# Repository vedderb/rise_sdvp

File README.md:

# VESC Self-Driving Model Vehicle Platform (formerly known as RISE SDVP)

This is the source code and hardware design for a model vehicle platform developed and maintained by the VESC project (formerly at RISE Research Institutes of Sweden). The platform has support for cars with Ackermann steering, robots with differential steering and partial support for quadcopters.

Self-Driving in this context means that the vehicles can follow a pre-programmed path outdoors accurately using RTK-GNSS. The paths can be edited using [RControlStation](Linux/RControlStation) as a set of points with different time stamps or velocities, depending on the mode. It is also possible to send paths to the vehicles with time stamps in real-time from external applications (either using UDP or TCP to RControlStation, or directly over a radio link) for e.g. following other vehicles.

Some details about the position estimation and the autopilot can be found in our [published article](https://www.hindawi.com/journals/jr/2018/4907536/).

Figure 1 shows a screenshot of RControlStation, which is a GUI where model vehicles can be viewed, configured and controlled in real time.

Here is a (quire outdated) video with a test of VESC SDVP on a model car:

## Repository Structure

The repository is organized as follows:

- **Documentation**  
    Contains Markdown files with documentation and tutorials, and the directories:
    - **PDF**  
    Contains generated PDFs from the markdown files. Will be cleared when the documentation is built.
    - **Pictures**  
    Contains photos and drawings, which are referenced in the documentation files.
- **Embedded**  
    Contains embedded software for various PCBs of the platform.
    - **Mote**  
    The software for the mote PCB, which can be used as a USB-to-802.15.4 bridge to communicate with the model cars.
    - **RC_Controller**  
    The software for the control PCB. This is where the sensor fusion, position estimation and autopilot for the car runs.
    - **uwb_board**  
    The software for the Ultra-wideband ranging boards.
- **Hardware**  
    KiCad PCB projects with the PCBs for the platform.
    - **Controller**  
    The PCB that is referred to as the controller in this documentation. The RC_Controller software runs on this one, and this is the main PCB that this platform is built on.
    - **RFMote_PA**  
    The USB-to-802.15.4 bridge mentioned above. Note that if an IP-connection with e.g. a raspberry pi is used, this one is not needed.
    - **uwb_pcb**  
    A PCB with a DWM1000 module, a STM32F4 microcontroller, a MPU9250 IMU, a CAN-transceiver and some DC/DC converters. The uwb_board software mentioned above runs on this one. This PCB is not needed, but it is useful for experimenting with UWB positioning.
- **Linux**  
    Contains Linux software, mostly written using the [Qt framework](https://www.qt.io/), for the platform.
    - **Car_Client**  
    This is a Qt command line program that can run on e.g. a raspberry pi, which is connected to the Controller PCB over USB. Car_Client provides a TCP bridge, which can be used to access the Controller over a network connection instead of a radio. Car_Client also runs the Chronos software (which might be documented later) and can simulate cars for development without having access to a model car. Car_Client can also connect to cameras supported by Video For Linux (V4L) and stream them as JPEG images to RControlStation.
    - **RControlStation**  
    This is a desktop program that can stream realtime data from the cars (including video), and edit trajectories for the model cars on top of OpenStreetMap. It can also act as a RTK base station, or connect to one. There are also many other functions, such as providing a TCP bridge to control cars and even emulating GPS signal using software-defined radio. It is a Qt Creator project, install the following packages under Ubuntu 18.04 or later to build it: `build-essential qtcreator qt5-default qtquickcontrols2-5-dev qtdeclarative5-dev libqt5serialport5-dev`
    - **RControlStationComm**  
    A C library that can be used to interface cars and trajectories from RControlStation, when using the TCP server in RControlStation.
    - **CarNetworkTester**  
    A test program where XML messages that can be decoded by RControlStation can be generated and sent, and the response can be studied. Useful for developing independent programs that interface with RControlStation and the model cars over TCP.
    - **scala_test**  
    Scala and java-based software to perform automatic testing of the model cars in real-time using ScalaCheck. RControlStationComm is used to interface with the cars and RControlStation. An interactive scala shell where the cars can be controlled, including the ability to generate trajectories to arbitrary points and orientations avoiding static obstacles, is also included. A paper where this is presented in detail is currently being written.
    - **Pi**  
    Scripts and UDEV rules for a raspberry pi (or similar) embedded Linux computer that is installed on a model car and runs Car_Client.

## Hardware

Figure 2 shows a hardware diagram of a working configuration of the VESC-SDVP platform. The cyan-colored boxes to the left are the components on a model car, and the green boxes to the right are a laptop computer connected over 4G to the model car. The laptop computer also runs a RTK-GNSS base station, so that the model car can position itself with around 3 cm accuracy relative to the GNSS antenna connected to the receiver on the laptop.

Here is a video that shows how a model car like the one in the block diagram above was built:

There are many different configuration of hardware components that can result in a working VESC SDVP model car. What they need to function in general is:

- The [Controller](Hardware/Controller), which runs the embedded software that controls the motion and estimates the position of the model car.
- A [VESC](https://vesc-project.com) motor controller that controls the motor on the car over CAN-bus, and provides speed and position estimation from the motor that is used in the sensor fusion in the controller.
- A computer that runs the [RControlStation](Linux/RControlStation) software.
- A way to communicate between the [Controller PCB](Hardware/Controller) and [RControlStation](Linux/RControlStation). The options are:
    - Using the embedded radios on the controller, and our [Radio Mote](Hardware/RFMote_PA) plugged in over USB to the computer running RControlStation.
    - Connecting the controller to an embedded Linux computer using USB, such as the [Raspberry PI](https://www.raspberrypi.org/), and running [Car_Client](Linux/Car_Client) on that computer. Then RControlStation can communicate with the controller over TCP using Car_Client. The TCP connection can then run over a network as usual, such as WiFi or 4G cellular. This is the method that we are using on the setup above.
- Correction data from a RTK-SN base station within 10 km from where the car operates. There is support for different sources of correction data, such as:
    - Connecting a supported GNSS receiver, such as the Ublox M8T or Ublox M8P, to the computer running RControlStation, and streaming correction data over that connection. This is what we do in the setup above.
    - Connecting to a NTRIP server. This can be done from RControlStation, or by passing an argument to Car_Client if it is used instead of a radio.
    - Our [Controller](Hardware/Controller) in base station mode, where it will transmit correction data over the 433 MHz radio.
- Other things that are (obviously) needed are motor, steering servo, power supplies and antennas.

## Steering Geometries

There is currently support for two different steering geometries: _Ackermann_ and _Differential_. In Ackermann steering mode there is one main motor driving the car, and a steering servo controlling the direction; whereas in differential mode there is one motor that drives the wheels on each side of the car and there is no steering servo. By default, the controller is configured for Ackermann steering, but that, and many other settings, can be changed in [conf_general.h](Embedded/RC_Controller/conf_general.h):

```
// Set to 1 to enable differential steering
#define HAS_DIFF_STEERING			1
// CAN ID of VESC motor controller for the left motor
#define DIFF_STEERING_VESC_LEFT		0
// CAN ID of VESC motor controller for the right motor
#define DIFF_STEERING_VESC_RIGHT	1
```

In addition to updating _conf_general.h_, geometry parameters for the car also have to be updated in RControlStation, as shown in Figure 3:

The most important parameters for Ackermann steering are listed in the following table. Some of them are not used in differential steering mode.

| Parameter      | Description             |
|--------------  |-----------------------------------------------------------------------------|
| Gear Ratio     | The ratio between one wheel revolution and one motor revolution.            |
| Turn Radius    | The radius of the circle the car follows at maximum steering angle.         |
| Wheel Diameter | Diameter of the model car wheels.                                           |
| Axis Distance  | Distance between front and rear wheel axis.                                 |
| Motor Poles    | Number of motor poles. Usually 2 or 4 for inrunners.                        |
| Servo Center   | PWM signal to output to steering servo when going straight [0 - 1].         |
| Servo Range    | Steering range. Negative numbers invert the servo direction [-1 - 1].       |

It is important to get these parameters correct, as they have a large impact on the position estimation and autopilot.

## Simulation Mode

It is possible to test the platform without having access to any other hardware than a computer. This can be done by running [Car_Client](Linux/Car_Client) with the following flags:

```
./Car_Client --usetcp --simulatecars 1:0
```

This will simulate a model car locally, including the autopilot. Then RControlStation can connecto to localhost over TCP and control the simulated car as if it were an actual model car. Car_Client accepts several different flags that affect the simulation; all flags can be listed using the -h argument:

```
./Car_Client -h
```

## Building and Running Car_Client

Car_Client can be built with

```
cd Linux/Car_Client
qmake -qt=5 DEFINES+=HAS_CAMERA
make clean
make
```
After that Car_Client can be started, and a connection can be made from RControlStation:

```
./Car_Client -p /dev/ttyACM0 --useudp --logusb --usetcp
```

## GPS Emulation using Software-Defined Radio (SDR)

RControlStation also supports generation GPS signals using the [Lime SDR](https://www.crowdsupply.com/lime-micro/limesdr-mini). This is work in progress and planned to be useful for automatic HIL testing in the future, but it might be nice to play around with if you have access to a Lime SDR. In order to use it, the [Lime Suite](https://wiki.myriadrf.org/Lime_Suite) has to be installed on your system. Once that is done, RControlStation can be build with Lime SDR support by uncommenting the following line in RControlStation.pro:

```
# Lime SDR support
#DEFINES += HAS_LIME_SDR
```

Once RControlStation is compiled with Lime SDR support, a real-time GPS simulation can be started from _Tests -> GPS Simulator_, which will show the dialog in Figure 4:

The desired latitude, longitude and height can then simply be set in the dialog. It is also possible to follow a model car and generate its perceived position. The [simulation mode](#SimulationMode) can also be used in combination with the GPS Emulator, making it possible to generate GPS signal for a virtual vehicle in real-time.

## User Guides, Tutorials and other Resources
- A work-in-progress user guide with several details on how to use RControlStation can be found [here](https://github.com/svenssonjoel/rise_sdvp_documentation/raw/master/RControlStationManual/RControlStation_doc_version_0_1.pdf).
- A tutorial on how to implement new functionality both in the embedded control software and in RControlStation can be found [here](https://github.com/svenssonjoel/rise_sdvp_documentation/raw/master/EmbeddedProgrammingExample/main.pdf)
- Our [published article](https://www.hindawi.com/journals/jr/2018/4907536/)

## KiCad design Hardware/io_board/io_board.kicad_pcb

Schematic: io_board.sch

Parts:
C1, C2, C3, C4, C17: 2.2u; C_0603_1608Metric
C9, C14, C15: 100u; CP_Radial_D10.0mm_P5.00mm
D1, D2, D5, D6, D7, D8: D_Schottky; D_SMA
D3: RED; LED_0603_1608Metric
D4: GREEN; LED_0603_1608Metric
H1, H2, H3, H4, H5: MountingHole; MountingHole_3.2mm_M3
J1, J2, J3: Valves; TerminalBlock_Phoenix_PT-1,5-2-5.0-H_1x02_P5.00mm_Horizontal
J4, J5: Steering; TerminalBlock_Phoenix_PT-1,5-2-5.0-H_1x02_P5.00mm_Horizontal
J6, J7: Limit SW; TerminalBlock_Phoenix_PT-1,5-2-5.0-H_1x02_P5.00mm_Horizontal
J8: ADC_IO; TerminalBlock_Phoenix_PT-1,5-2-5.0-H_1x02_P5.00mm_Horizontal
J9, J10: ADC_VDIV; TerminalBlock_Phoenix_PT-1,5-2-5.0-H_1x02_P5.00mm_Horizontal
J11: 12V IN; TerminalBlock_Phoenix_PT-1,5-2-5.0-H_1x02_P5.00mm_Horizontal
J12, J15: CAN; JST_PH_B4B-PH-K_1x04_P2.00mm_Vertical
J13: AS5047; JST_PH_B6B-PH-K_1x06_P2.00mm_Vertical
Q1, Q2, Q3, Q4, Q5, Q6, Q7, Q8, Q9, Q10, Q11, Q12, Q13: Q_NMOS_GSD; SOT-23
R1, R2, R3, R6, R7, R9, R12, R14, R17, R20, R23: 10k; R_0603_1608Metric
R4, R5, R10, R11, R13, R15, R16, R18, R19, R21, R22, R24, R25: 1k; R_0603_1608Metric
R8: 220R; R_0603_1608Metric
U1: AZ1117-3.3; SOT-223
U2: TJA1051TK-3; DFN-8-1EP_3x3mm_P0.65mm_EP1.55x2.4mm

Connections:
+5V: C1.1, C17.1, J12.4, J15.4, U1.3, U2.3 (VCC)
+12V: C9.1, C14.1, D1.1 (K), D2.1 (K), D5.1 (K), D6.1 (K), D7.1 (K), D8.1 (K), J5.1, J11.1, R10.1
/ADC1: J8.1; also elsewhere on the board
/ADC2: J8.2; also elsewhere on the board
/ADC_DIV1: R14.2, R15.1; also elsewhere on the board
/ADC_DIV2: R17.2, R18.1; also elsewhere on the board
/ADC_DIV3: R20.2, R21.1; also elsewhere on the board
/ADC_DIV4: R23.2, R24.1; also elsewhere on the board
/AS_CS: J13.5; also elsewhere on the board
/AS_MISO: J13.4; also elsewhere on the board
/AS_MOSI: J13.2; also elsewhere on the board
/AS_SCK: J13.3; also elsewhere on the board
/CANH: J12.3, J15.3, R8.1, U2.7 (CANH)
/CANL: J12.2, J15.2, R8.2, U2.6 (CANL)
/CAN_RX: U2.4 (RXD); also elsewhere on the board
/CAN_TX: U2.1 (TXD); also elsewhere on the board
/LED_GREEN: D4.2 (A); also elsewhere on the board
/LED_RED: D3.2 (A); also elsewhere on the board
/LIM1: J7.2, R16.2; also elsewhere on the board
/LIM2: J7.1, R19.2; also elsewhere on the board
/LIM3: J6.2, R22.2; also elsewhere on the board
/LIM4: J6.1, R25.2; also elsewhere on the board
/SP: R12.2, R13.1; also elsewhere on the board
/VALVE1: Q1.1 (G), Q2.1 (G), R1.1; also elsewhere on the board
/VALVE2: Q3.1 (G), Q4.1 (G), R2.1; also elsewhere on the board
/VALVE3: Q5.1 (G), Q6.1 (G), R3.1; also elsewhere on the board
/VALVE4: Q7.1 (G), Q8.1 (G), R6.1; also elsewhere on the board
/VALVE5: Q9.1 (G), Q10.1 (G), R7.1; also elsewhere on the board
/VALVE6: Q11.1 (G), Q13.1 (G), R9.1; also elsewhere on the board
/VALVE_STEERING: Q12.1 (G); also elsewhere on the board
GND: C1.2, C2.2, C3.2, C4.2, C9.2, C14.2, C15.2, C17.2, J5.2, J11.2, J12.1, J13.6, J15.1, Q1.2 (S), Q2.2 (S), Q3.2 (S), Q4.2 (S), Q5.2 (S), Q6.2 (S), Q7.2 (S), Q8.2 (S), Q9.2 (S), Q10.2 (S), Q11.2 (S), Q12.2 (S), Q13.2 (S), R1.2, R2.2, R3.2, R4.1, R5.1, R6.2, R7.2, R9.2, R13.2, R15.2, R18.2, R21.2, R24.2, U1.1, U2.2 (GND), U2.8 (S), U2.9 (GND); also elsewhere on the board
unnamed: C4.1, J4.1, R11.1
unnamed: D1.2 (A), J1.1, Q1.3 (D), Q2.3 (D)
unnamed: D2.2 (A), J1.2, Q3.3 (D), Q4.3 (D)
unnamed: D3.1 (K), R4.2
unnamed: D4.1 (K), R5.2
unnamed: D5.2 (A), J2.1, Q5.3 (D), Q6.3 (D)
unnamed: D6.2 (A), J2.2, Q7.3 (D), Q8.3 (D)
unnamed: D7.2 (A), J3.1, Q9.3 (D), Q10.3 (D)
unnamed: D8.2 (A), J3.2, Q11.3 (D), Q13.3 (D)
unnamed: J4.2, R12.1
unnamed: J9.1, R14.1
unnamed: J9.2, R17.1
unnamed: J10.1, R20.1
unnamed: J10.2, R23.1
unnamed: Q12.3 (D), R10.2, R11.2
VCC: C2.1, C3.1, C15.1, J13.1, R16.1, R19.1, R22.1, R25.1, U1.2, U2.5 (VIO); also elsewhere on the board

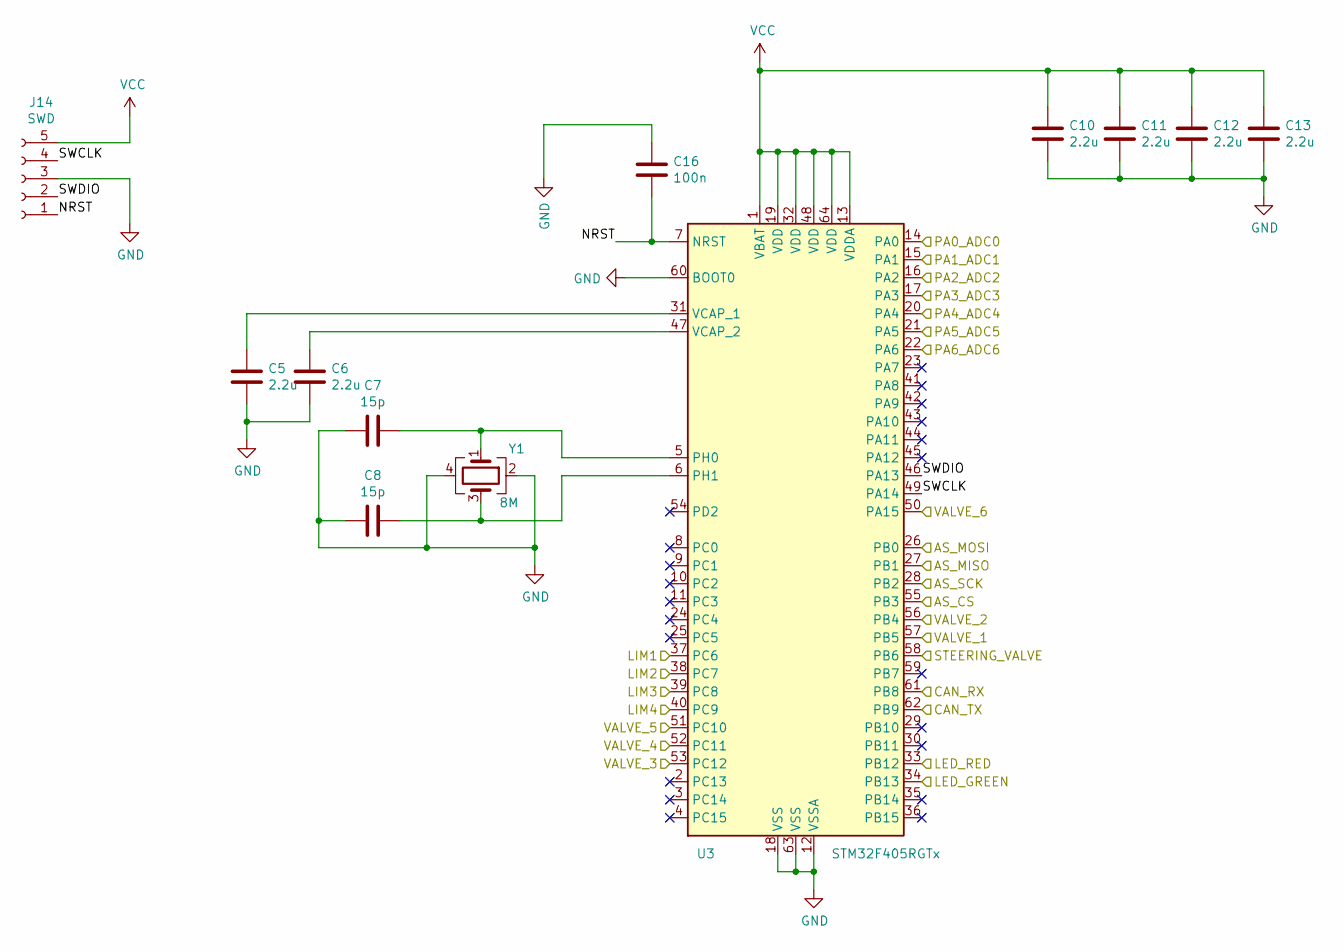
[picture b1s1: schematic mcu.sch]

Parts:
C5, C6, C10, C11, C12, C13: 2.2u; C_0603_1608Metric
C7, C8: 15p; C_0603_1608Metric
C16: 100n; C_0603_1608Metric
J14: SWD; JST_PH_B5B-PH-K_1x05_P2.00mm_Vertical
U3: STM32F405RGTx; LQFP-64_10x10mm_P0.5mm
Y1: 8M; Crystal_SMD_Abracon_ABM3C-4Pin_5.0x3.2mm

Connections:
/ADC1: U3.20 (PA4); also elsewhere on the board
/ADC2: U3.21 (PA5); also elsewhere on the board
/ADC_DIV1: U3.14 (PA0); also elsewhere on the board
/ADC_DIV2: U3.15 (PA1); also elsewhere on the board
/ADC_DIV3: U3.16 (PA2); also elsewhere on the board
/ADC_DIV4: U3.17 (PA3); also elsewhere on the board
/AS_CS: U3.55 (PB3); also elsewhere on the board
/AS_MISO: U3.27 (PB1); also elsewhere on the board
/AS_MOSI: U3.26 (PB0); also elsewhere on the board
/AS_SCK: U3.28 (PB2); also elsewhere on the board
/CAN_RX: U3.61 (PB8); also elsewhere on the board
/CAN_TX: U3.62 (PB9); also elsewhere on the board
/LED_GREEN: U3.34 (PB13); also elsewhere on the board
/LED_RED: U3.33 (PB12); also elsewhere on the board
/LIM1: U3.37 (PC6); also elsewhere on the board
/LIM2: U3.38 (PC7); also elsewhere on the board
/LIM3: U3.39 (PC8); also elsewhere on the board
/LIM4: U3.40 (PC9); also elsewhere on the board
/SP: U3.22 (PA6); also elsewhere on the board
/VALVE1: U3.57 (PB5); also elsewhere on the board
/VALVE2: U3.56 (PB4); also elsewhere on the board
/VALVE3: U3.53 (PC12); also elsewhere on the board
/VALVE4: U3.52 (PC11); also elsewhere on the board
/VALVE5: U3.51 (PC10); also elsewhere on the board
/VALVE6: U3.50 (PA15); also elsewhere on the board
/VALVE_STEERING: U3.58 (PB6); also elsewhere on the board
/mcu/NRST: C16.2, J14.1, U3.7 (NRST)
/mcu/SWCLK: J14.4, U3.49 (PA14)
/mcu/SWDIO: J14.2, U3.46 (PA13)
GND: C5.2, C6.2, C7.2, C8.2, C10.2, C11.2, C12.2, C13.2, C16.1, J14.3, U3.12 (VSSA), U3.18 (VSS), U3.60 (BOOT0), U3.63 (VSS), Y1.2, Y1.4; also elsewhere on the board
unnamed: C5.1, U3.31 (VCAP_1)
unnamed: C6.1, U3.47 (VCAP_2)
unnamed: C7.1, U3.5 (PH0), Y1.1
unnamed: C8.1, U3.6 (PH1), Y1.3
VCC: C10.1, C11.1, C12.1, C13.1, J14.5, U3.1 (VBAT), U3.13 (VDDA), U3.19 (VDD), U3.32 (VDD), U3.48 (VDD), U3.64 (VDD); also elsewhere on the board

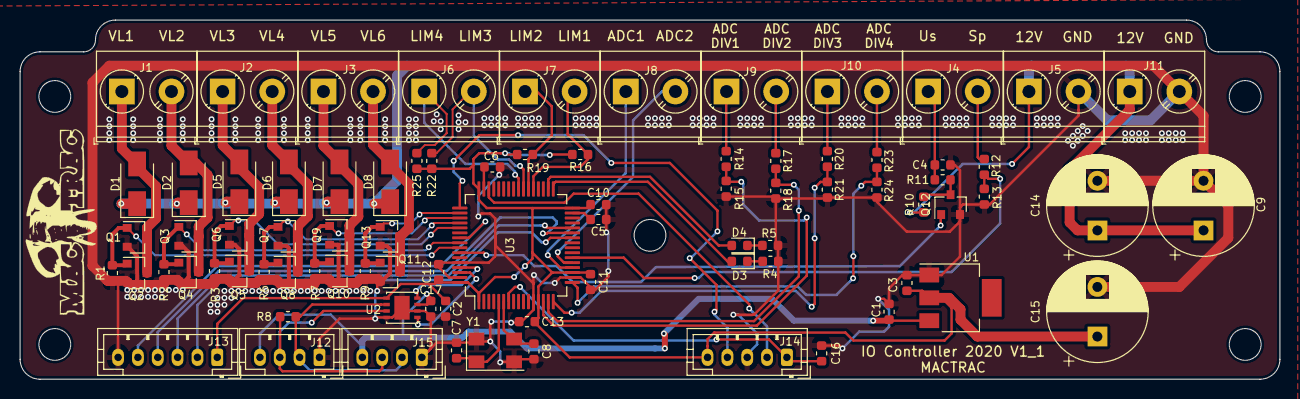
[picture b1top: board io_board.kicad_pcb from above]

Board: 2 copper layers, 127.0 x 36.2 mm, 87 parts (0 on the bottom side), 54 nets.

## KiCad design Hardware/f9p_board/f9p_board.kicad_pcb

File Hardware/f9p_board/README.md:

## UBLOX ZED F9P based positioning controller (Work in progress!).

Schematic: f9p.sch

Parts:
C22: 100n; C_0603_1608Metric
C23, C24, C25: 2.2u; C_0603_1608Metric
D1: RED; LED_0603_1608Metric
L2: 56n; L_0603_1608Metric
R3: 100K; R_0603_1608Metric
R4, R5: 22R; R_0603_1608Metric
R11: 1k; R_0603_1608Metric
R12: 4.7R; R_0603_1608Metric
U1: Ublox_ZED_F9P; UBLOX_ZED_F9P
U7: uFL_conn; U.FL_Molex_MCRF_73412-0110_Vertical

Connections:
F9P_3v3: R3.1, U1.38 (V_USB); also elsewhere on the board
F9P_RESET_N: U1.49 (RESET_N); also elsewhere on the board
F9P_USB_DM: R4.1; also elsewhere on the board
F9P_USB_DP: R5.1; also elsewhere on the board
GND: C22.2, C23.1, C24.1, C25.1, R3.2, R11.2, U1.0, U1.1 (GND), U1.3 (GND), U1.12 (GND), U1.14 (GND), U1.32 (GND), U1.37 (GND), U1.41 (GND), U1.48 (GND), U7.2; also elsewhere on the board
MCU_RX_F9P_TX: U1.42 (TXD_SPI_MISO); also elsewhere on the board
MCU_TX_F9P_RX: U1.43 (RXD_SPI_MOSI); also elsewhere on the board
unnamed: C22.1, L2.2, R12.2
unnamed: D1.1, R11.1
unnamed: D1.2, U1.20 (RTK_STAT)
unnamed: L2.1, U1.2 (RF_IN_1), U7.1
unnamed: R4.2, U1.39 (USB_DM)
unnamed: R5.2, U1.40 (USB_DP)
unnamed: R12.1, U1.7 (VCC_RF)
TIMEPULSE: U1.53 (TIMEPULSE); also elsewhere on the board
VCC: C23.2, C24.2, C25.2, U1.33 (VCC), U1.34 (VCC), U1.36 (V_BCKP); also elsewhere on the board

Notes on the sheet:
DSEL 1 (or open) | 0 42 UART TX | SPI_MISO 43 UART RX | SPI_MOSI 44 I2C Data | SPI CS 45 I2C_CLOCK | SPI_CLK
Host-interface UART
Correction UART RX/TX
Output
Input (Active low)
Input (Active high)

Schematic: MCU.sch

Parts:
C8, C9: 15p; C_0603_1608Metric
C10, C11, C12, C13, C14, C15, C16, C17, C18, C19, C20, C26: 2.2u; C_0603_1608Metric
C21: 100n; C_0603_1608Metric
D2: RED; LED_0603_1608Metric
D3: GREEN; LED_0603_1608Metric
H1, H2, H3, H4: MountingHole; MountingHole_3.2mm_M3
J1, J2: USB_B_Mini; USB_Mini-B_Lumberg_2486_01_Horizontal
J4: CAN; JST_PH_B4B-PH-K_1x04_P2.00mm_Vertical
J7: SERV_0; PinHeader_1x03_P2.54mm_Vertical
J8: SERV_1; PinHeader_1x03_P2.54mm_Vertical
J9: SERV_2; PinHeader_1x03_P2.54mm_Vertical
J10: SERV_3; PinHeader_1x03_P2.54mm_Vertical
P1: SWD; JST_PH_B6B-PH-K_1x06_P2.00mm_Vertical
R6, R7, R9, R10: 1k; R_0603_1608Metric
R8, R21, R22, R23, R24: 220R; R_0603_1608Metric
R13, R14: 22R; R_0603_1608Metric
SW3: BOOT0; SW_SPDT_PCM12
U2: STM32F405RGTx; LQFP-64_10x10mm_P0.5mm
U5: BMI160; Bosch_LGA-14_3x2.5mm_P0.5mm; digikey 828-1057-1-ND
U6: TJA1051TK-3; DFN-8-1EP_3x3mm_P0.65mm_EP1.55x2.4mm
Y1: 8Mhz; Crystal_SMD_5032-4Pin_5.0x3.2mm

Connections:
CANH: J4.3, R8.1, U6.7
CANL: J4.2, R8.2, U6.6
CAN_RX: U2.61, U6.4
CAN_TX: U2.62, U6.1
F9P_RESET_N: U2.40; also elsewhere on the board
F9P_USB_DM: J1.2; also elsewhere on the board
F9P_USB_DP: J1.3; also elsewhere on the board
F9P_USB_VBUS: J1.1; also elsewhere on the board
GND: C8.1, C9.1, C10.2, C11.2, C12.2, C13.2, C14.2, C15.2, C16.2, C17.2, C18.2, C19.2, C20.2, C21.1, C26.1, D2.1, D3.1, J1.5, J1.6, J2.5, J2.6, J4.1, J7.3, J8.3, J9.3, J10.3, P1.4, SW3.1, U2.12, U2.18, U2.28, U2.63, U5.1, U5.6, U5.7, U6.2, U6.8, U6.9, Y1.2, Y1.4; also elsewhere on the board
IMU_INT2: U2.57, U5.9
LED0: R6.2, U2.51
LED1: R7.2, U2.52
MCU_RX_F9P_TX: U2.38; also elsewhere on the board
MCU_TX_F9P_RX: U2.37; also elsewhere on the board
MCU_USB_DM: J2.2, R13.1
MCU_USB_DP: J2.3, R14.1
MCU_USB_VBUS: J2.1; also elsewhere on the board
NRST: C21.2, P1.2, U2.7
unnamed: C8.2, U2.6, Y1.3
unnamed: C9.2, U2.5, Y1.1
unnamed: C10.1, U2.31
unnamed: C11.1, U2.47
unnamed: D2.2, R6.1
unnamed: D3.2, R7.1
unnamed: J7.1, R21.1
unnamed: J8.1, R22.1
unnamed: J9.1, R23.1
unnamed: J10.1, R24.1
unnamed: R13.2, U2.44
unnamed: R14.2, U2.45
unnamed: R21.2, U2.26
unnamed: R22.2, U2.27
unnamed: SW3.2, U2.60
PWR_5V: C26.2, J4.4, J7.2, J8.2, J9.2, J10.2, U2.42, U6.3; also elsewhere on the board
SCL: R10.2, U2.29, U5.13
SDA: R9.2, U2.30, U5.14
SERV_2: R23.2, U2.16
SERV_3: R24.2, U2.17
SWCLK: P1.5, U2.49
SWDIO: P1.3, U2.46
TIMEPULSE: U2.39; also elsewhere on the board
VCC: C12.1, C13.1, C14.1, C15.1, C16.1, C17.1, C18.1, C19.1, C20.1, P1.6, R9.1, R10.1, SW3.3, U2.1, U2.13, U2.19, U2.32, U2.48, U2.64, U5.5, U5.8, U5.12, U6.5; also elsewhere on the board
VOLT_METER: U2.8; also elsewhere on the board

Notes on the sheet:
place close to pin 1, 19, 32, 48, 64, 13
Dubbelkoll CSB - VCC. vi ska ha I2c
Place near VDD/GND BMI160
PC0 - PC5 has ADC
Servo connectors

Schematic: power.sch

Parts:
C1, C2, C5, C6, C7, C35, C36, C37: 2.2u; C_0603_1608Metric
C3: 100n; C_0603_1608Metric
C4: 100u; CP_EIA-3528-12_Kemet-T
C27: 0.01u; C_0603_1608Metric
C28, C29, C30, C31: 2.2u; C_1206_3216Metric
C32: 4700p; C_0603_1608Metric
C33, C40: 0.1u; C_0603_1608Metric
C34: 47p; C_0603_1608Metric
C38: 100u; CP_Radial_D10.0mm_P5.00mm
C39: 470u; CP_Radial_D10.0mm_P5.00mm
J3: BAT_CONN; TerminalBlock_Phoenix_PT-1,5-2-5.0-H_1x02_P5.00mm_Horizontal
J5: USB_A_PWR_OUTPUT; USB_A_Stewart_SS-52100-001_Horizontal
J6: EN_BAT_VIN; JST_PH_B2B-PH-K_1x02_P2.00mm_Vertical
L1: 22u; L_Taiyo-Yuden_MD-5050
L3: 7.2u; L_12x12mm_H8mm
Q1: DMN62D0UW-7; SOT-323_SC-70
R1: 33k; R_0603_1608Metric
R2: 10k; R_0603_1608Metric
R15: 243k; R_0603_1608Metric
R16: 16.9k; R_0603_1608Metric
R17: 39k; R_0603_1608Metric
R18: 2.2k; R_0603_1608Metric
R19: 53.6k; R_0603_1608Metric
R20: 10.2k; R_0603_1608Metric
SW1: F9P_USB_POWER; SW_SPDT_PCM12
SW2: MCU_USB_POWER; SW_SPDT_PCM12
U3: MCP16311MS; MSOP-8_3x3mm_P0.65mm
U4: ncv8705; WDFN6
U8: TPS54561DPRR; TI-DPR; digikey 296-40803-1-ND
U9: PDS760-13; POWERDI5

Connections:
BAT_VIN: C28.1, C29.1, C30.1, C31.1, C38.1, J3.2, R17.1, U8.2
F9P_3v3: C6.1, U4.1; also elsewhere on the board
F9P_USB_VBUS: C7.1, SW1.1, U4.4, U4.6; also elsewhere on the board
FB: R19.1, R20.2, U8.6
GND: C1.2, C2.2, C4.2, C5.2, C6.2, C7.2, C27.2, C28.2, C29.2, C30.2, C31.2, C32.2, C34.2, C35.2, C36.2, C37.2, C38.2, C39.2, C40.2, J3.1, J5.4, J5.5, J6.1, R2.1, R15.2, R18.2, R20.1, U3.5, U3.8, U4.3, U4.GND, U8.8, U8.11, U9.1, U9.2; also elsewhere on the board
MCU_USB_VBUS: SW2.1; also elsewhere on the board
unnamed: C2.1, U3.2
unnamed: C3.1, U3.7
unnamed: C3.2, L1.2, U3.6
unnamed: C27.1, U8.4
unnamed: C32.1, R16.2
unnamed: C33.1, U8.1
unnamed: C34.1, R16.1, U8.7
unnamed: J6.2, U8.3
unnamed: Q1.3, R17.2
unnamed: R1.1, R2.2, U3.1
unnamed: R15.1, U8.5
PWR_5V: C1.1, C35.1, C36.1, C37.1, C39.1, J5.1, L3.2, Q1.1, R19.2, SW1.2, SW2.2, U3.3, U3.4; also elsewhere on the board
SW: C33.2, L3.1, U8.9, U9.3
VCC: C4.1, C5.1, L1.1, R1.2; also elsewhere on the board
VOLT_METER: C40.1, Q1.2, R18.1; also elsewhere on the board

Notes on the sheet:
5v USB Power
3.3V and max 0.5A
3.3V and 1A
The EN pin has an internal pull-up that enables the TPS54561 if the pin is left flaoting.
Kanske behövs sådär 1206 capar
https://katalog.we-online.de/pbs/datasheet/7447709100.pdf
3.2V at 60V BAT_VIN
12061C225KAT2A CAP CER 2.2UF 100V X7R 1206 C3216X7S2A225K160AB CAP CER 2.2UF 100V X7S 1206
RHS = RLS * ((VOUT - 0.8) / 0.8) RHS = RLS * ((5 - 0.8) / 0.8) RHS = RLS * (4.2 / 0.8) RHS = RLS * 5.25 53.55 = 10.2 * 5.25
RHS
RLS
Compensating for the smaller caps with a larger electrolyte

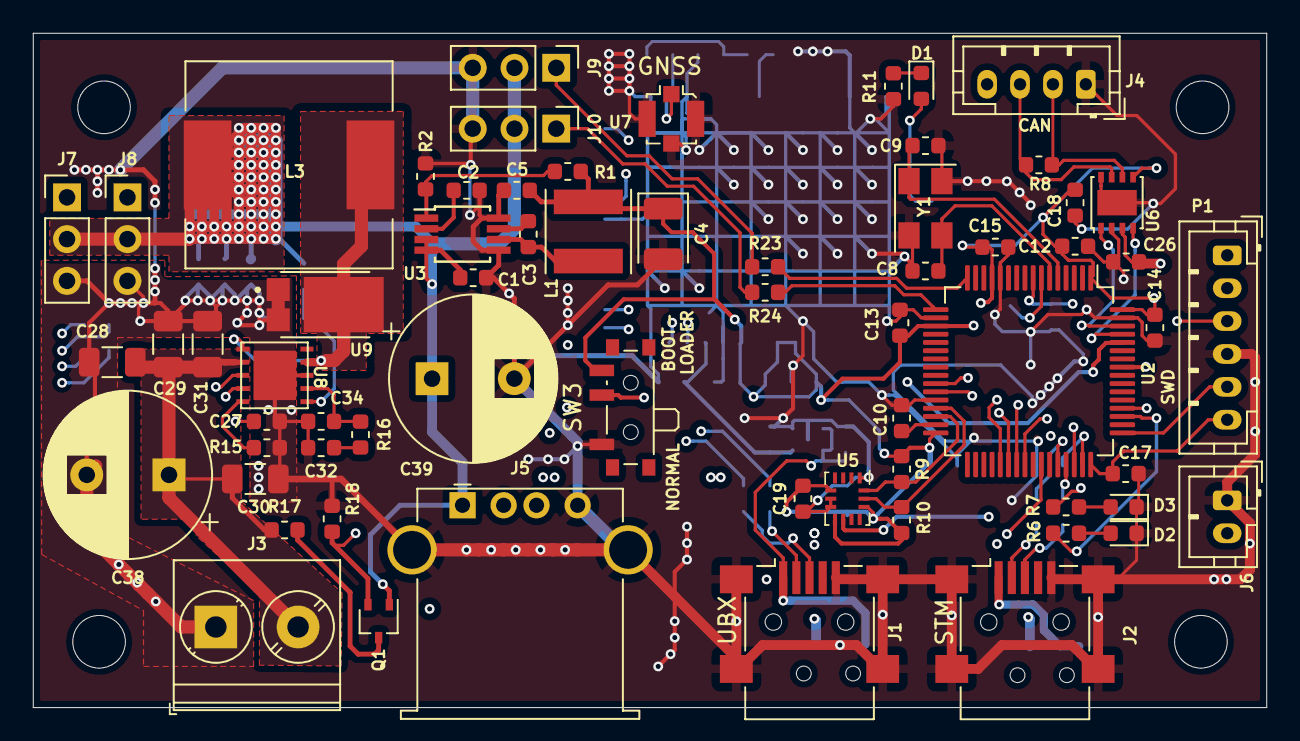
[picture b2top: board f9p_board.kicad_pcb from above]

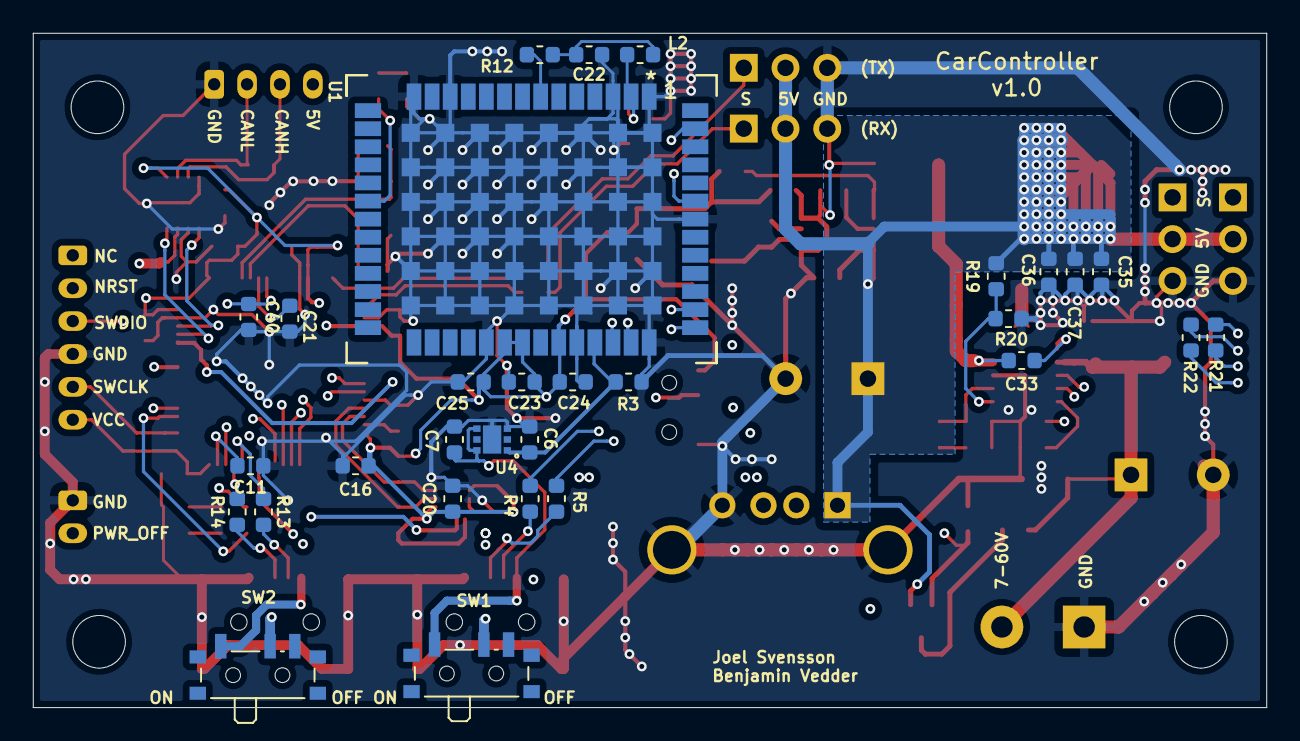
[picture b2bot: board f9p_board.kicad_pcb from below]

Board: 4 copper layers, 75.0 x 41.0 mm, 99 parts (30 on the bottom side), 65 nets.

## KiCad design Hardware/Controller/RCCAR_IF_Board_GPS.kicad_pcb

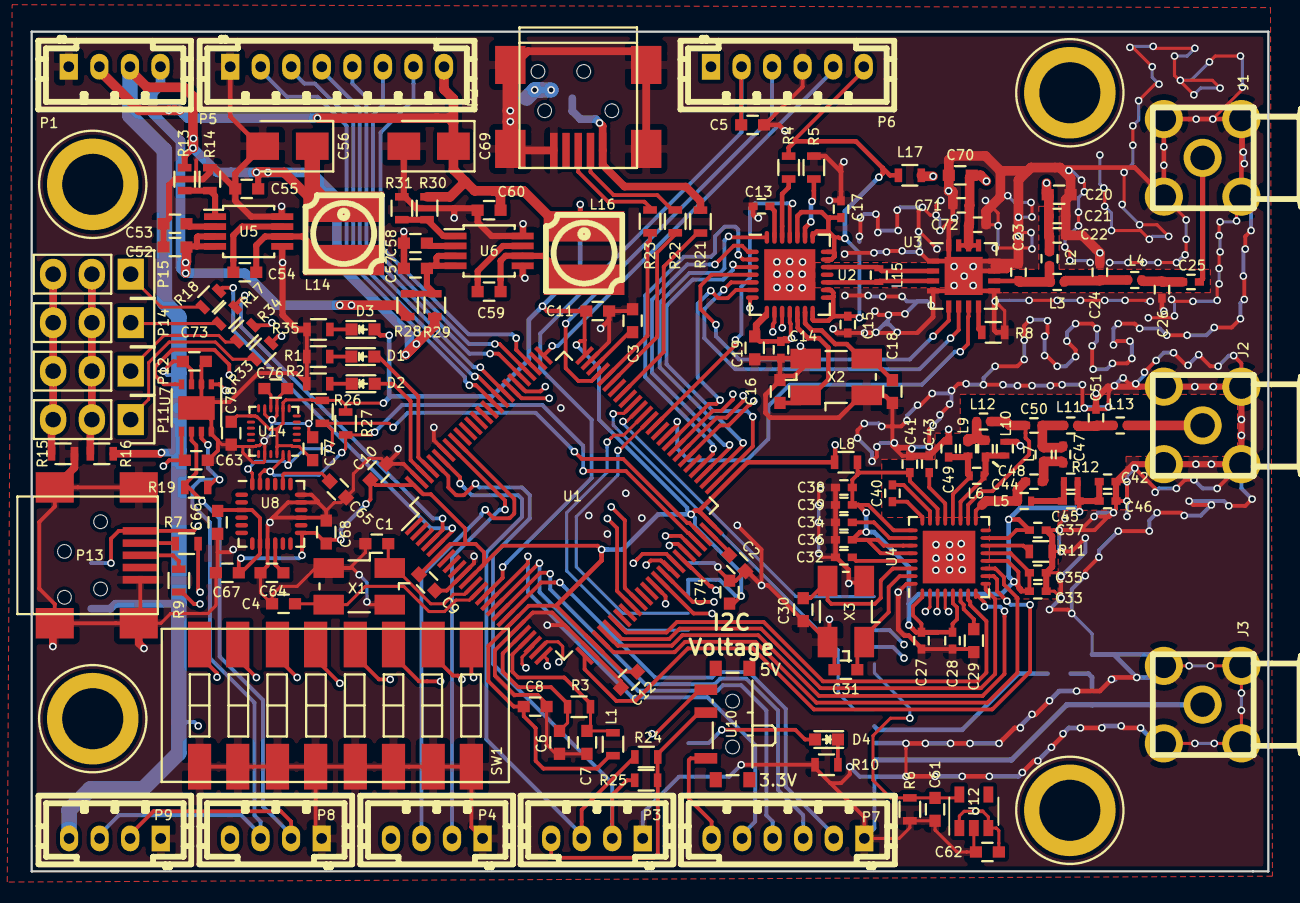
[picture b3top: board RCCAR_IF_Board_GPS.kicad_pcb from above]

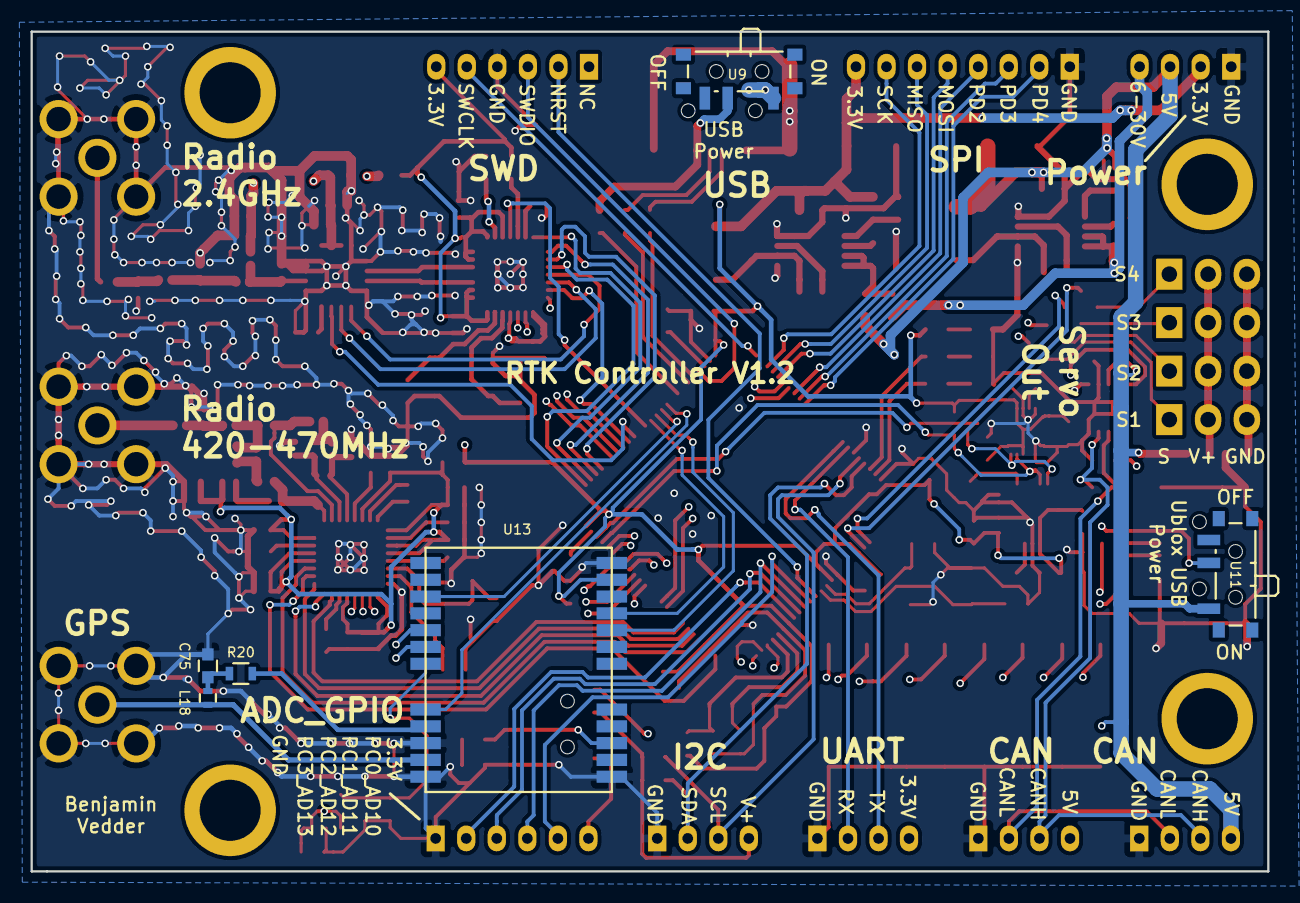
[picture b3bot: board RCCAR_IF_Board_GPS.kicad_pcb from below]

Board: 4 copper layers, 81.0 x 55.0 mm, 173 parts (6 on the bottom side), 143 nets.

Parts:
1PIN, 1PIN#2, 1PIN#3, 1PIN#4: P***; 1pin_4mm
C1, C4, C16, C18, C30, C31: 15p; C_0603
C2, C3, C6, C7, C8, C9, C10, C11, C12, C19, C20, C29, C52, C53, C55, C57, C58, C60, C61, C62, C63, C64, C66, C67, C68, C70, C73, C74, C77, C78: 2.2u; C_0603
C5, C54, C59, C65, C75, C76: 100n; C_0603
C13, C14, C15, C17, C27, C28, C32, C33, C34, C35, C36, C37, C38, C39, C41, C42, C43: 100n; C_0402
C21, C71: 1n; C_0402
C22, C72: 12p; C_0402
C23, C24, C47: 2.2p; C_0402
C25: 18p; C_0402
C26: 0.2p; C_0402
C40: 1.8n; C_0402
C44: 39p; C_0402
C45: 56p; C_0402
C46: 100p; C_0402
C48, C49, C50: 5.1p; C_0402
C51: 6.2p; C_0402
C56, C69: 100u; Tantalum_Case-B_EIA-3528-21_Wave
D1, D4: RED; LED_0603
D2: GREEN; LED_0603
D3: BLUE; LED_0603
J1, J2, J3: SMA; sma_90_crf
L1, L8, L17: BEAD; R_0603
L2: 4.7n; R_0402
L3: 1n; R_0402
L4: 2n; R_0402
L5, L6, L18: 56n; R_0402
L7, L12: 15n; R_0402
L9, L10: 27n; R_0402
L11: 43n; R_0402
L13: 22n; R_0402
L14, L16: 22U; inductor_smd_4.8x2.8mm
L15: DNM; R_0402
P1: POWER; b4b-ph-kl
P2: USB_STM; USB_Mini-B
P3: I2C; b4b-ph-kl
P4: UART; b4b-ph-kl
P5: NRF_SPI; b8b-ph-kl
P6: SWD; b6b-ph-kl
P7: ADC_GPIO; b6b-ph-kl
P8, P9: CAN; b4b-ph-kl
P11: OUT_1; Pin_Header_Straight_1x03
P12: OUT_2; Pin_Header_Straight_1x03
P13: USB_UBLOX; USB_Mini-B
P14: OUT_3; Pin_Header_Straight_1x03
P15: OUT_4; Pin_Header_Straight_1x03
R1, R2, R6, R10, R24, R25, R26, R27, R35: 1k; R_0603
R3: 4R7; R_0603
R4, R14, R31: 10k; R_0603
R5, R11: 56k; R_0603
R7, R9, R21, R22, R23: 22R; R_0603
R8: 3.9k; R_0603
R12: 18R; R_0402
R13: 52.3k; R_0603
R15, R16, R28, R29: 0R; R_0603
R17, R18, R19, R33, R34: 220R; R_0603
R20: 4.7R; R_0603
R30: 33k; R_0603
SW1: Address; SW_DIP_SMD_x8_Slide
U1: STM32F40X_LQFP100; LQFP-100_14x14mm_Pitch0.5mm
U2: CC2520; QFN-28-1EP_5x5mm_Pitch0.5mm
U3: CC2592; QFN-16-1EP_4x4mm_Pitch0.65mm
U4: CC1120; QFN-32-1EP_5x5mm_Pitch0.5mm
U5, U6: MCP16311/2; MSOP-8_3x3mm_Pitch0.65mm
U7: TJA1051TK3; DFN-8-1EP_3x3mm_Pitch0.65mm
U8: MPU9150; QFN-24-1EP_4x4mm_Pitch0.5mm
U9, U11: USB_SUPPLY; SW_SPDT_PCM12
U10: I2C_VOLTAGE; SW_SPDT_PCM12
U12: AP131-33; SOT-23-5
U13: ublox_neo_m8p; ublox_neo
U14: MPU9250; QFN-24_3x3mm_Pitch0.4mm
X1: 8M; Crystal_SMD_5032_4Pads
X2, X3: 32M; Crystal_SMD_5032_4Pads

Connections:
+5V: C55.1, C56.1, C73.1, L14.1, P1.3, P8.4, P9.4, R13.2, R16.1, R29.2, U7.3, U9.1, U10.3, U11.1
+BATT: C52.1, P1.4, R28.2, U5.3, U5.4
/CAN/CANH: P8.3, P9.3, R19.1, U7.7
/CAN/CANL: P8.2, P9.2, R19.2, U7.6
/CAN/CAN_RX: U1.81, U7.4
/CAN/CAN_TX: U1.82, U7.1
/CC1120/CS_N: U1.29, U4.11
/CC1120/GPIO0: U1.26, U4.10
/CC1120/GPIO2: U1.25, U4.4
/CC1120/GPIO3: U1.24, U4.3
/CC1120/V_REG: C27.1, C28.1, C33.1, C35.1, C36.1, C37.1, C38.1, C39.1, C41.1, C42.1, C45.2, C46.1, L8.1, R12.2, U4.1, U4.5, U4.12, U4.13, U4.15, U4.22, U4.25, U4.27, U4.28
/CC2520/CC_CS_N: U1.51, U2.3
/CC2520/CC_GPIO0: U1.56, U2.10
/CC2520/CC_GPIO1: U1.57, U2.9
/CC2520/CC_GPIO2: U1.58, U2.7
/CC2520/CC_GPIO3: U1.59, U2.6
/CC2520/CC_RESET: U1.62, U2.25
/CC2520/CC_SCLK: U1.52, U2.28
/CC2520/CC_SI: U1.54, U2.2
/CC2520/CC_SO: U1.53, U2.1
/CC2520/HGM: U1.60, U3.7
/CC2520/LNA_EN: U2.5, U3.6
/CC2520/PA_EN: U2.4, U3.5
/CC2520/VDD_CC2592: C20.2, C21.2, C22.2, C70.2, C71.2, C72.2, L2.2, L17.2, U3.13, U3.14, U3.15
/MCU/NRST: C5.2, P6.2, U1.14
/MCU/PA0: U1.23, U4.2
/MCU/PA5_SCK1: U1.30, U4.8
/MCU/PA6_MISO1: U1.31, U4.9
/MCU/PA7_MOSI1: U1.32, U4.7
/MCU/PB6_TX1: P4.3, U1.92
/MCU/PB7_RX1: P4.2, U1.93
/MCU/PB8_SCL1: P3.3, R24.2, U1.95
/MCU/PB9_SDA1: P3.2, R25.2, U1.96
/MCU/PB10_SCL2: R27.1, U1.47, U8.23, U14.23
/MCU/PB11_SDA2: R26.1, U1.48, U8.24, U14.24
/MCU/PC0_ADC123_IN10: P7.5, U1.15
/MCU/PC1_ADC123_IN11: P7.4, U1.16
/MCU/PC2_ADC123_IN12: P7.3, U1.17
/MCU/PC3_ADC123_IN13: P7.2, U1.18
/MCU/PC6_TX6: U1.63, U13.21
/MCU/PC7_RX6: U1.64, U13.20
/MCU/PC8: U1.65, U13.3
/MCU/PC9: U1.66, U13.8
/MCU/PC10_SCK3: P5.7, U1.78
/MCU/PC11_MISO3: P5.6, U1.79
/MCU/PC12_MOSI3: P5.5, U1.80
/MCU/PD2: P5.4, U1.83
/MCU/PD3: P5.3, U1.84
/MCU/PD4: P5.2, U1.85
/MCU/PE0: D1.2, U1.97
/MCU/PE1: D2.2, U1.98
/MCU/PE8: SW1.16, U1.39
/MCU/PE9: SW1.15, U1.40
/MCU/PE10: SW1.14, U1.41
/MCU/PE11: SW1.13, U1.42
/MCU/PE12: SW1.12, U1.43
/MCU/PE13: SW1.11, U1.44
/MCU/PE14: SW1.10, U1.45
/MCU/PE15: SW1.9, U1.46
/MCU/SWCLK: P6.5, U1.76
/MCU/SWDIO: P6.3, U1.72
/MCU/USB_DM: R22.1, U1.70
/MCU/USB_DP: R23.1, U1.71
/MCU/USB_VP: R21.1, U1.68
/SERVO_IO/OUT_1: R33.2, U1.35
/SERVO_IO/OUT_2: R34.2, U1.36
/SERVO_IO/OUT_3: R17.2, U1.4
/SERVO_IO/OUT_4: R18.2, U1.5
/ublox/RTK_STAT: D4.2, U13.15
/ublox/USB_DM: R7.2, U13.5
/ublox/USB_DP: R9.2, U13.6
/ublox/VDD_USB: C61.1, R6.1, U12.5, U13.7
GND: C1.2, C2.1, C3.1, C4.2, C5.1, C6.2, C7.1, C8.1, C9.1, C10.1, C11.1, C12.1, C13.1, C14.1, C15.1, C16.2, C17.1, C18.2, C19.1, C20.1, C21.1, C22.1, C23.1, C24.1, C26.1, C27.2, C28.2, C29.1, C30.1, C31.1, C32.1, C33.2, C34.1, C35.2, C36.2, C37.2, C38.2, C39.2, C41.2, C42.2, C43.2, C46.2, C49.1, C51.2, C52.2, C53.2, C55.2, C56.2, C57.2, C58.2, C60.2, C61.2, C62.2, C63.2, C64.2, C65.2, C66.1, C67.1, C68.1, C69.2, C70.1, C71.1, C72.1, C73.2, C74.2, C75.2, C76.2, C77.2, C78.2, J1.2, J2.2, J3.2, L10.1, P1.1, P2.5, P2.6, P3.1, P4.1, P5.1, P6.4, P7.1, P8.1, P9.1, P13.5, P13.6, R1.2, R2.2, R5.2, R6.2, R8.2, R10.2, R11.2, R14.1, R15.1, R31.1, R35.2, SW1.1, SW1.2, SW1.3, SW1.4, SW1.5, SW1.6, SW1.7, SW1.8, U1.10, U1.20, U1.27, U1.74, U1.94, U1.99, U2.29, U3.1, U3.4, U3.9, U3.11, U3.12, U3.16, U3.17, U4.32, U4.33, U5.5, U5.8, U6.5, U6.8, U7.2, U7.8, U7.9, U8.9, U8.15, U8.17, U8.18, U12.2, U13.10, U13.12, U13.13, U13.24, U14.9, U14.11, U14.18, U14.20, X1.3, X2.3, X3.3
unnamed: C1.1, U1.12, X1.1
unnamed: C2.2, U1.49
unnamed: C3.2, U1.73
unnamed: C4.1, U1.13, X1.2
unnamed: C6.1, R3.2, U1.21
unnamed: C7.2, L1.2, R3.1, U1.22
unnamed: C13.2, U2.27
unnamed: C16.1, U2.12, X2.1
unnamed: C18.1, U2.13, X2.2
unnamed: C23.2, L2.1, L3.1, U3.10
unnamed: C24.2, L3.2, L4.1
unnamed: C25.1, C26.2, L4.2
unnamed: C25.2, J1.1
unnamed: C29.2, U4.6
unnamed: C30.2, U4.30, X3.2
unnamed: C31.2, U4.31, X3.1
unnamed: C32.2, U4.29
unnamed: C34.2, U4.26
unnamed: C40.1, U4.24
unnamed: C40.2, U4.23
unnamed: C43.1, U4.21
unnamed: C44.1, C47.2, L7.2
unnamed: C44.2, L5.1, U4.17
unnamed: C45.1, L5.2, R12.1
unnamed: C47.1, C50.2, L7.1, L11.2
unnamed: C48.1, L9.1, L12.1
unnamed: C48.2, L6.2, L10.2, U4.19
unnamed: C49.2, L6.1, L9.2, U4.20
unnamed: C50.1, L12.2, U4.18
unnamed: C51.1, L11.1, L13.2
unnamed: C53.1, U5.2
unnamed: C54.1, U5.7
unnamed: C54.2, L14.2, U5.6
unnamed: C57.1, R28.1, R29.1, U6.3, U6.4
unnamed: C58.1, U6.2
unnamed: C59.1, U6.7
unnamed: C59.2, L16.2, U6.6
unnamed: C62.1, P13.1, U11.2, U12.1, U12.3
unnamed: C64.1, U8.10
unnamed: C65.1, U8.20
unnamed: C75.1, L18.1, R20.1
unnamed: C76.1, U14.10
unnamed: D1.1, R1.1
unnamed: D2.1, R2.1
unnamed: D3.1, R35.1
unnamed: D4.1, R10.1
unnamed: J2.1, L13.1
unnamed: J3.1, L18.2, U13.11
unnamed: L15.1, U2.19, U3.2
unnamed: L15.2, U2.17, U3.3
unnamed: P2.1, R21.2, U9.2
unnamed: P2.2, R22.2
unnamed: P2.3, R23.2
unnamed: P3.4, R24.1, R25.1, U10.2
unnamed: P11.1, R33.1
unnamed: P11.2, P12.2, P14.2, P15.2, R16.2
unnamed: P11.3, P12.3, P14.3, P15.3, R15.2
unnamed: P12.1, R34.1
unnamed: P13.2, R7.1
unnamed: P13.3, R9.1
unnamed: P14.1, R17.1
unnamed: P15.1, R18.1
unnamed: R4.2, U2.26
unnamed: R5.1, U2.23
unnamed: R8.1, U3.8
unnamed: R11.1, U4.14
unnamed: R13.1, R14.2, U5.1
unnamed: R20.2, U13.9
unnamed: R30.1, R31.2, U6.1
VCC: C8.2, C9.2, C10.2, C11.2, C12.2, C14.2, C15.2, C17.2, C19.2, C60.1, C63.1, C66.2, C67.2, C68.2, C69.1, C74.1, C77.1, C78.1, D3.2, L1.1, L8.2, L16.1, L17.1, P1.2, P4.4, P5.8, P6.6, P7.6, R4.1, R26.2, R27.2, R30.2, U1.6, U1.11, U1.19, U1.28, U1.50, U1.75, U1.100, U2.8, U2.11, U2.14, U2.15, U2.16, U2.20, U2.21, U2.22, U2.24, U7.5, U8.3, U8.8, U8.13, U10.1, U13.22, U13.23, U14.1, U14.8, U14.13, U14.22
